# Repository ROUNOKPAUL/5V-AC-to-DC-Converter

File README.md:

⚡ 5V AC to DC Converter

📌 Overview

This project demonstrates the conversion of an AC input into DC output using a bridge rectifier circuit and a filter capacitor. It is designed to demonstrate the fundamental principles of rectification, filtering, and DC power supply circuits.

The circuit uses four 1N4007 diodes arranged in a bridge rectifier configuration to convert AC into pulsating DC. A capacitor is then used to reduce ripple, while an LED indicates the presence of power.

🎯 Project Objectives

Convert AC voltage into DC voltage.

Understand the working principle of a bridge rectifier.

Reduce output voltage ripple using a filter capacitor.

Indicate power availability using an LED.

Design a circuit schematic and PCB using KiCad.

⚙️ Components Used

Component

Specification

Quantity

Diodes

1N4007

4

Capacitor

1000 µF

1

Resistor

2.2 kΩ

1

Resistor

10 kΩ

1

LED

5 mm

1

Terminal Block

2-pin

2

🔌 Circuit Design

The circuit consists of three main stages:

Bridge Rectifier: Four 1N4007 diodes convert AC input into pulsating DC.

Filtering Stage: A 1000 µF capacitor smooths the rectified output by reducing voltage ripple.

Indicator Stage: An LED with a current-limiting resistor indicates power availability.

🔄 Working Principle

1. AC Input

The AC voltage is supplied through the input terminal block.

2. Rectification

The four diodes form a full-wave bridge rectifier. Both halves of the AC waveform are converted into the same polarity at the output.

3. Filtering

The 1000 µF capacitor charges during the rectification process and discharges between peaks, helping to provide a smoother DC voltage.

4. Power Indication

The LED connected with a 2.2 kΩ resistor acts as a visual indicator of power at the circuit.

🛠️ Tools Used

KiCad – Schematic design and PCB layout.

Electronic Components – For circuit implementation and testing.

📷 Project Preview

Add your schematic, PCB layout and physical circuit photos here.

🚀 Future Improvements

Add a voltage regulator for a stable 5V DC output.

Improve filtering to reduce voltage ripple.

Perform PCB layout optimisation.

Test the circuit under different load conditions.

⚠️ Safety Note
This circuit is intended for educational purposes. AC voltage can be dangerous. Use an appropriately isolated, low-voltage AC source for testing. Do not connect the circuit directly to mains electricity.

The circuit shown does not include a voltage regulator, so the output is not guaranteed to be a regulated 5V DC supply.
This circuit is intended for educational purposes. AC voltage can be dangerous. Use an appropriately isolated, low-voltage AC source for testing. Do not connect the circuit directly to mains electricity.

The circuit shown does not include a voltage regulator, so the output is not guaranteed to be a regulated 5V DC supply.

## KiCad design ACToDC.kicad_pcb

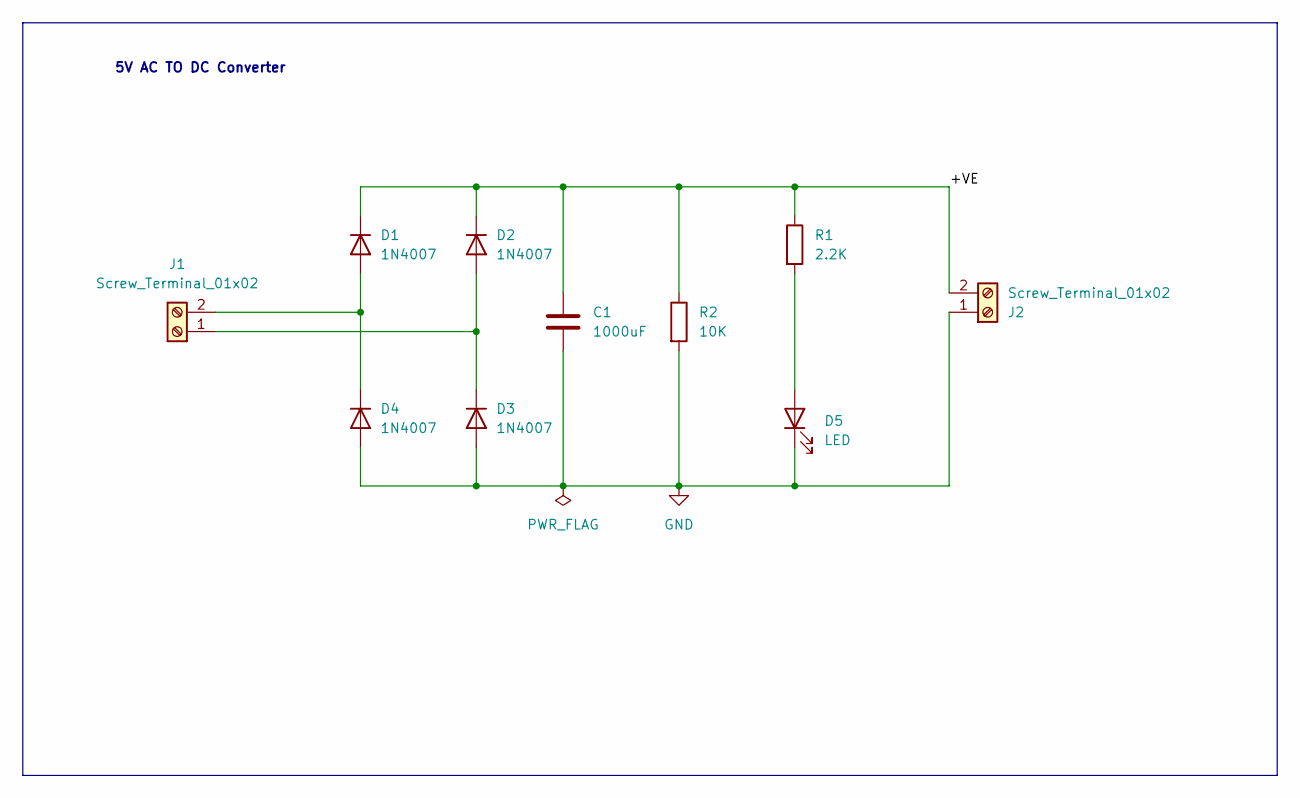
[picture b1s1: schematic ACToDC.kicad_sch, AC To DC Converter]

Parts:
C1: 1000uF; C_Radial_D8.0mm_H11.5mm_P3.50mm
D1, D2, D3, D4: 1N4007; D_DO-41_SOD81_P10.16mm_Horizontal
D5: LED; LED_D5.0mm
J1, J2: Screw_Terminal_01x02; TerminalBlock_MaiXu_MX126-5.0-02P_1x02_P5.00mm
R1: 2.2K; R_Axial_DIN0204_L3.6mm_D1.6mm_P7.62mm_Horizontal
R2: 10K; R_Axial_DIN0204_L3.6mm_D1.6mm_P7.62mm_Horizontal

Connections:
/+VE: C1.1, D1.1 (K), D2.1 (K), J2.2, R1.1, R2.1
GND: C1.2, D3.2 (A), D4.2 (A), D5.1 (K), J2.1, R2.2
unnamed: D1.2 (A), D4.1 (K), J1.2
unnamed: D2.2 (A), D3.1 (K), J1.1
unnamed: D5.2 (A), R1.2

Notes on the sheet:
5V AC TO DC Converter

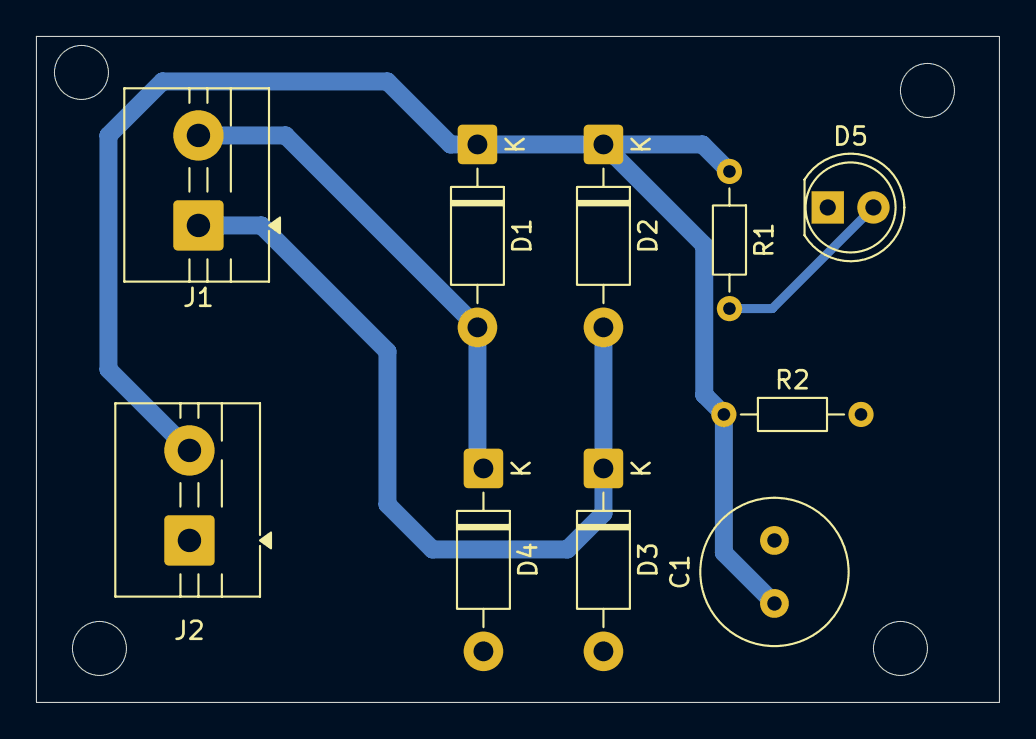
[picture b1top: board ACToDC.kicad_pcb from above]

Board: 2 copper layers, 53.5 x 37.0 mm, 10 parts (0 on the bottom side), 5 nets.
